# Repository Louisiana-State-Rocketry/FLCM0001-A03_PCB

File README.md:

# Eclipse_2_PCB
PCB Files for the Eclipse 2 Flight Computer.

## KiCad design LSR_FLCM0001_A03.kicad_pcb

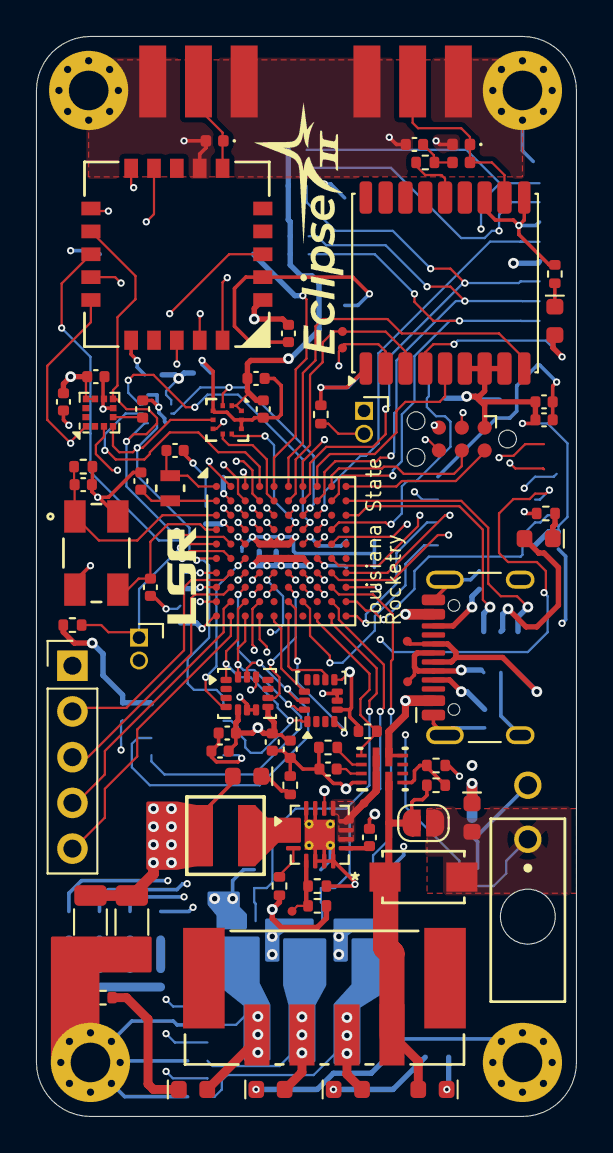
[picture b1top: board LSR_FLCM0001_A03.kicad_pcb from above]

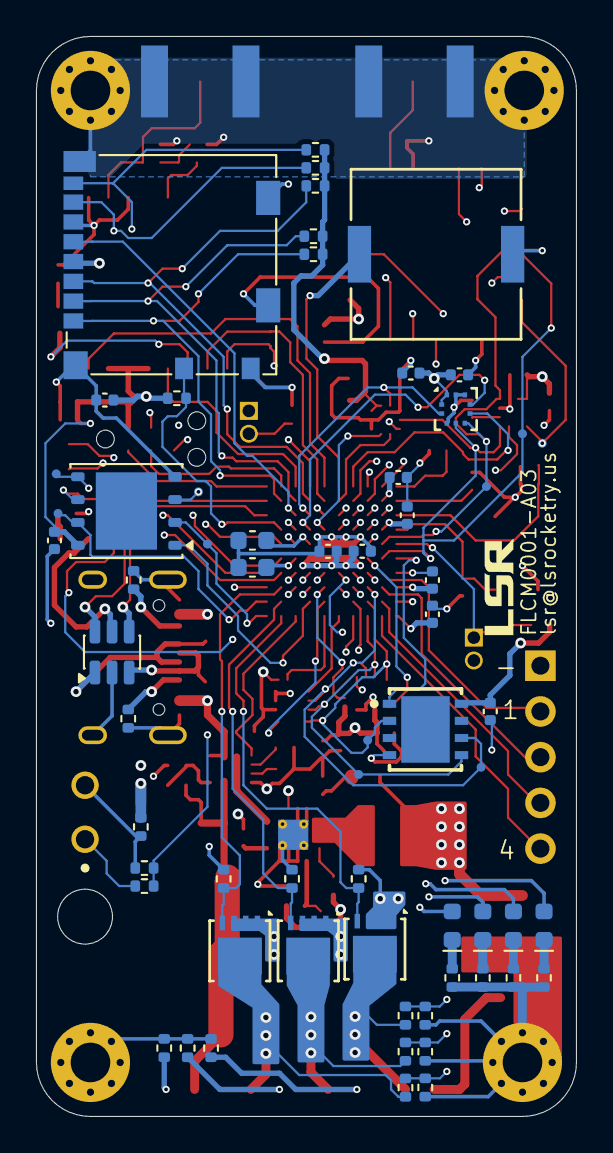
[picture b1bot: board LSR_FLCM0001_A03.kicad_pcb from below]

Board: 6 copper layers, 30.0 x 60.0 mm, 145 parts (63 on the bottom side), 111 nets.

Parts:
C1, C2: C_Small_US; C_0603_1608Metric
C3, C4, C5, C6, C7, C8, C9, C10, C11, C12, C13, C14, C15, C16, C17, C20, C21, C22, C23, C24, C25, C26, C27, C28, C29, C30, C31, C32, C34: C_Small_US; C_0402_1005Metric
C18, C19: C_Small_US; C_1206_3216Metric
C33: C_Small; C_0402_1005Metric
CR1: B340A-13-F; DIODE_SODB340_2P92X4P6_DIO
D1, D2, D5, D6, D9, D10, D11, D13: Yellow; LED_0603_1608Metric_Yellow
D3, D4, D7, D8: Red; LED_0603_1608Metric_Red
D12, D14: D_TVS_Small; D_0402_1005Metric
FB1: FerriteBead_Small; L_0402_1005Metric
H1, H2, H3, H4: MountingHole_2.2mm_M2_Pad_Via
IC1: FM25L04B-DG; SON95P400X450X80-9N-R270X370
J1: USB_C_Receptacle_USB2.0_16P; USB_C_Receptacle_HCTL_HC-TYPE-C-16P-01A
J2, J3: Conn_01x02_Pin; PinSocket_1x02_P1.27mm_Vertical
J4: Conn_ARM_SWD_TagConnect_TC2030-NL; Tag-Connect_TC2030-IDC-NL_2x03_P1.27mm_Vertical
J5: Micro_SD_Card_Det2; microSD_HC_Molex_104031-0811
J6: 2125280200; CONN_2125280000_02_MOL
J7: 1771114; CONN_1814728
J8: Conn_01x05_Pin; PinHeader_1x05_P2.54mm_Vertical
J9, J10: SMA_Edge; SMA_Edge_8mm
JP1: SolderJumper-2_P1.3mm_Open_RoundedPad1.0x1.5mm
L1: 2.2uH; IND_COILCRAFT_XAL4020
LS1: CPT-9019A-SMT-TR; CPT-9019A_CUD
Q1, Q2, Q3: AON7296; DFN3X3A_8L_EPA1_P_AOS
R1, R2, R3, R4, R5, R6, R7, R8, R9, R10, R11, R12, R13, R14, R15, R16, R17, R18, R19, R20, R21, R22, R23, R24, R25, R26, R27, R28, R29, R30, R31, R32, R33, R34, R35, R36, R37, R38, R39, R40, R41, R42: R_Small_US; R_0402_1005Metric
TP1, TP2, TP3, TP4, TP5, TP6, TP7, TP8, TP9, TP10, TP11, TP12, TP13, TP14, TP15, TP16, TP17, TP18: TestPoint; TestPoint-0.5mm
U1: USBLC6-2SC6; SOT-23-6
U2: STM32H742VGH6; TFBGA-100_8x8mm_Layout10x10_P0.8mm
U3: W25Q128JVP; WSON-8-1EP_6x5mm_P1.27mm_EP3.4x4.3mm
U4: TPS62130A; VQFN-16-1EP_3x3mm_P0.5mm_EP1.68x1.68mm_ThermalVias
U5: TPS2121RUXR; RUX0012A
U6: LSM6DSM; LGA-14_3x2.5mm_P0.5mm_LayoutBorder3x4y
U7: LSM6DS320; LGA-14_3x2.5mm_P0.5mm_LayoutBorder3x4y
U8: LIS2MDL; LGA-12_2x2mm_P0.5mm
U9, U10: BMP390; 10LGA_2X2X0p75_BOS
U11: MAX-M10S; ublox_MAX
U12: E22-900MM22S; E22-900MM22S_BYT
XTAL1: 9HT11-32.768KDZB-T; XTAL_68KDZB-T_TXC
Y1: ABM3B-24.000MHZ; CRYSTAL_ABM3B_ABR

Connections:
+3V3: C3.1, C4.1, C5.1, C6.1, C7.1, C8.1, C13.1, C14.1, C15.1, C18.1, C19.1, C20.1, C21.1, C22.1, C23.1, C24.1, C26.1, C27.1, C28.1, C29.1, C30.1, C31.1, C32.1, C34.1, D7.2 (A), IC1.8 (VDD), J3.1, J4.1 (VCC), J5.4 (VDD), L1.2, R3.2, R12.1, R13.1, R14.1, R15.1, R16.1, R17.2, R22.2, R24.2, R28.2, TP18.1 (1_1), U2.B2 (VBAT), U2.D2 (VDD), U2.F4 (VDDLDO), U2.F5 (VDD), U2.F6 (VDD33_USB), U2.F7 (PDR_ON), U2.H1 (VDDA), U2.K1 (VDD), U3.8 (VCC), U4.14 (VOS), U6.5 (VDDIO), U6.8 (VDD), U7.5 (VDDIO), U7.8 (VDD), U8.9 (Vdd), U8.10 (Vdd_IO), U9.1 (VDDIO), U9.10 (VDD), U10.1 (VDDIO), U10.10 (VDD), U11.6 (V_BCKP), U11.7 (VCC_IO), U11.8 (VCC), U12.1 (VCC)
/ADC1_INP4: R36.2, R37.2, U2.G4 (ADC1_INP4)
/ADC1_INP8: R32.2, R33.2, U2.H4 (ADC1_INP8)
/ADC1_INP9: R34.2, R35.2, U2.J4 (ADC1_INP9)
/BMP_{1}.INT: U2.D6 (PD7), U10.7 (INT)
/BMP_{2}.INT: U2.D7 (PD4), U9.7 (INT)
/Connectors/CC1: J1.A5 (CC1), R2.2
/Connectors/CC2: J1.B5 (CC2), R1.2
/Connectors/D+: J1.A6 (D+), J1.B6 (D+), TP3.1 (1_1), U1.1 (I/O1)
/Connectors/D-: J1.A7 (D-), J1.B7 (D-), TP2.1 (1_1), U1.3 (I/O2)
/EBYTE.BUSY: U2.B4 (PB8), U12.11 (BUSY)
/EBYTE.CS: U2.A2 (PC13), U12.14 (NSS)
/EBYTE.DIO1: U2.C5 (PB5), U12.20 (DIO1)
/EBYTE.DIO2: U2.B3 (PE3), U12.19 (DIO2)
/EBYTE.DIO3: U2.C3 (PE4), U12.18 (DIO3)
/EBYTE.NRST: U2.D3 (PE5), U12.3 (NRST)
/EBYTE.RXEN: U2.C4 (PE1), U12.10 (RXEN)
/EBYTE.TXEN: U2.D4 (PE0), U12.9 (TXEN)
/GPS.EXTINT: U2.A8 (PA15), U11.5 (EXTINT)
/GPS.~RESET: U2.A6 (PB4), U11.9 (~RESET)
/LIS2MDL.CS: U2.G3 (PA4), U8.3 (~CS)
/LSM6DSM.CS: U2.K5 (PE9), U6.12 (CS)
/LSM6DSM.INT1: U2.J6 (PE12), U6.4 (INT1)
/LSM6DSM.INT2: U2.K6 (PE13), U6.9 (INT2)
/LSM6DSV320XTR.CS: U2.G6 (PE10), U7.12 (CS)
/LSM6DSV320XTR.INT1: U2.F3 (PC3_C), U7.4 (INT1)
/LSM6DSV320XTR.INT2: U2.H6 (PE11), U7.9 (INT2)
/MCU/ADC_BATT: R5.1, R6.2, U2.K4 (ADC1_INP5)
/MCU/BATT_LED: D1.1 (K), R8.2
/MCU/BOOT0: J3.2, R4.2, U2.D5 (BOOT0)
/MCU/Buzzer_PWM: LS1.1, U2.A5 (TIM4_CH2)
/MCU/NRST: J2.1, J4.3 (~RESET), R3.1, U2.E1 (NRST)
/MCU/PD14: D1.2 (A), U2.H8 (PD14)
/MCU/PD15: D2.2 (A), U2.G8 (PD15)
/MCU/PE14: D3.2 (A), U2.G7 (PE14)
/MCU/PE15: D4.2 (A), U2.H7 (PE15)
/MCU/Power_LED_3V3: D3.1 (K), R10.2
/MCU/Power_LED_VIN: D4.1 (K), R11.2
/MCU/RCC_OSC32_IN: C11.1, U2.A1 (RCC_OSC32_IN), XTAL1.1
/MCU/RCC_OSC32_OUT: C12.1, U2.B1 (RCC_OSC32_OUT), XTAL1.2
/MCU/RCC_OSC_IN: C9.1, R7.2, U2.C1 (RCC_OSC_IN), Y1.1
/MCU/RCC_OSC_OUT: C10.1, U2.D1 (RCC_OSC_OUT), Y1.3
/MCU/SWCLK: J4.4 (SWCLK), U2.A9 (DEBUG_JTCK-SWCLK)
/MCU/SWDIO: J4.2 (SWDIO), U2.A10 (DEBUG_JTMS-SWDIO)
/MCU/SWO: J4.6 (SWO), U2.A7 (DEBUG_JTDO-SWO)
/MCU/USB_LED: D2.1 (K), R9.2
/MCU/VCAP1: C1.1, U2.E7 (VCAP)
/MCU/VCAP2: C2.1, U2.F8 (VCAP)
/Power/BATT_LED: D5.1 (K), R20.2
/Power/CP2: R18.1, R19.2, U5.3 (CP2)
/Power/FB: R24.1, R25.2, TP16.1 (1_1), U4.5 (FB)
/Power/ILM: R26.2, U5.10 (ILM)
/Power/PG: R22.1, U4.4 (PG)
/Power/Power_LED_3V3: D7.1 (K), R23.2
/Power/Power_LED_VIN: D8.1 (K), R27.2
/Power/SS: C17.1, U5.11 (SS)
/Power/SS/TR: C16.1, U4.9 (SS/TR)
/Power/TPS2121.SW: L1.1, U4.1 (SW), U4.2 (SW), U4.3 (SW)
/Power/USB_LED: D6.1 (K), R21.2
/Pyro/Pyro_{1}_Charge: D11.2 (A), J7.1, Q3.5, Q3.6, Q3.7, Q3.8, Q3.9, R36.1
/Pyro/Pyro_{1}_LED: D11.1 (K), R40.2
/Pyro/Pyro_{2}_Charge: D9.2 (A), J7.2, Q1.5, Q1.6, Q1.7, Q1.8, Q1.9, R32.1
/Pyro/Pyro_{2}_LED: D9.1 (K), R38.2
/Pyro/Pyro_{3}_Charge: D10.2 (A), J7.3, Q2.5, Q2.6, Q2.7, Q2.8, Q2.9, R34.1
/Pyro/Pyro_{3}_LED: D10.1 (K), R39.2
/Pyro_{1}_Gate: Q3.4, R31.1, U2.K9 (PD8)
/Pyro_{2}_Gate: Q1.4, R30.1, U2.J9 (PD9)
/Pyro_{3}_Gate: Q2.4, R29.1, U2.H9 (PD10)
/QUADSPI_BK1_IO0: TP7.1 (1_1), U2.G9 (QUADSPI_BK1_IO0), U3.5 (DI/IO_{0})
/QUADSPI_BK1_IO1: TP8.1 (1_1), U2.K10 (QUADSPI_BK1_IO1), U3.2 (DO/IO_{1})
/QUADSPI_BK1_IO2: TP4.1 (1_1), U2.A3 (QUADSPI_BK1_IO2), U3.3 (~WP/IO_{2})
/QUADSPI_BK1_IO3: TP9.1 (1_1), U2.J10 (QUADSPI_BK1_IO3), U3.7 (~HOLD/~RESET/IO_{3})
/QUADSPI_BK1_NCS: U2.J7 (QUADSPI_BK1_NCS), U3.1 (~CS)
/QUADSPI_CLK: U2.G5 (QUADSPI_CLK), U3.6 (CLK)
/SDMMC1_CK: J5.5 (CLK), U2.C8 (SDMMC1_CK)
/SDMMC1_CMD: J5.3 (CMD), R14.2, U2.B7 (SDMMC1_CMD)
/SDMMC1_D0: J5.7 (DAT0), R13.2, U2.F9 (SDMMC1_D0)
/SDMMC1_D1: J5.8 (DAT1), R12.2, U2.E9 (SDMMC1_D1)
/SDMMC1_D2: J5.1 (DAT2), R16.2, U2.B9 (SDMMC1_D2)
/SDMMC1_D3: J5.2 (DAT3/CD), R15.2, U2.B8 (SDMMC1_D3)
/SD_DET: J5.9 (DET_B), R17.1, U2.D9 (PA8)
/SPI1_MISO: IC1.2 (SO), TP11.1 (1_1), U2.J3 (SPI1_MISO), U6.1 (SDO/SA0), U7.1 (SDO/SA0)
/SPI1_MOSI: IC1.5 (SI), TP12.1 (1_1), U2.K3 (SPI1_MOSI), U6.14 (SDA), U7.14 (SDA)
/SPI1_SCK: IC1.6 (SCK), TP10.1 (1_1), U2.H3 (SPI1_SCK), U6.13 (SCL), U7.13 (SCL)
/SPI2_MISO: TP14.1 (1_1), U2.E2 (SPI2_MISO), U8.7 (DRDY), U9.5 (SDO), U10.5 (SDO), U12.12 (MISO)
/SPI2_MOSI: TP15.1 (1_1), U2.F2 (SPI2_MOSI), U8.4 (SDA/SDI/SDO), U9.4 (SDI), U10.4 (SDI), U12.13 (MOSI)
/SPI2_SCK: TP13.1 (1_1), U2.C7 (SPI2_SCK), U8.1 (SCL/SPC), U9.2 (SCK), U10.2 (SCK), U12.15 (SCK)
/ST: R28.1, U2.K8 (PB12), U5.9 (ST)
/Sensors/Magnetometer/C1: C25.1, U8.5 (C1)
/Sensors/RF/EBYTE.ANT: D12.1 (A1), J9.1 (In), U12.6 (ANT)
/Sensors/RF/GPS.RF_{Filter}: C33.1, FB1.2, R42.2
/Sensors/RF/GPS.TIMEPULSE: D13.2 (A), U11.4 (TIMEPULSE)
/Sensors/RF/RF_IN: D14.1 (A1), FB1.1, J10.1 (In), U11.11 (RF_IN)
/Sensors/RF/Timepulse_LED: D13.1 (K), R41.2
/Sensors/RF/VCC_RF: R42.1, U11.14 (VCC_RF)
/TIM2_CH1: J8.2, U2.G2 (TIM2_CH1)
/TIM2_CH2: J8.3, U2.H2 (TIM2_CH2)
/TIM2_CH3: J8.4, U2.J2 (TIM2_CH3)
/TIM2_CH4: J8.5, U2.K2 (TIM2_CH4)
/USART2_RX: TP6.1 (1_1), U2.C6 (USART2_RX), U11.2 (TXD)
/USART2_TX: TP5.1 (1_1), U2.B6 (USART2_TX), U11.3 (RXD)
/USB_OTG_FS_DM: U1.4 (I/O2), U2.C10 (USB_OTG_FS_DM)
/USB_OTG_FS_DP: U1.6 (I/O1), U2.B10 (USB_OTG_FS_DP)
/~BMP_{1.CS}: U2.B5 (PB6), U10.6 (CSB)
/~BMP_{2.CS}: U2.A4 (PB9), U9.6 (CSB)
/~FRAM.CS: IC1.1 (~CS), U2.F1 (PC0)
GND: C1.2, C2.2, C3.2, C4.2, C5.2, C6.2, C7.2, C8.2, C9.2, C10.2, C11.2, C12.2, C13.2, C14.2, C15.2, C16.2, C17.2, C18.2, C19.2, C20.2, C21.2, C22.2, C23.2, C24.2, C25.2, C26.2, C27.2, C28.2, C29.2, C30.2, C31.2, C32.2, C33.2, C34.2, D12.2 (A2), D14.2 (A2), H1.1, H2.1, H3.1, H4.1, IC1.4 (VSS), J1.A1 (GND), J1.A12 (GND), J1.B1 (GND), J1.B12 (GND), J1.SH (SHIELD), J2.2, J4.5 (GND), J5.6 (VSS), J5.10 (DET_A), J5.SH (SHIELD), J6.2, J8.1, J9.2 (Ext), J10.2 (Ext), LS1.2, Q1.1, Q1.2, Q1.3, Q2.1, Q2.2, Q2.3, Q3.1, Q3.2, Q3.3, R1.1, R2.1, R4.1, R6.1, R7.1, R8.1, R9.1, R10.1, R11.1, R19.1, R20.1, R21.1, R23.1, R25.1, R26.1, R27.1, R29.2, R30.2, R31.2, R33.1, R35.1, R37.1, R38.1, R39.1, R40.1, R41.1, U1.2 (GND), U2.C2 (VSS), U2.E4 (VSS), U2.E5 (VSS), U2.E6 (VSS), U2.G1 (VSSA), U2.J1 (VSS), U3.4 (GND), U4.6 (GND), U4.7 (FSW), U4.8 (DEF), U4.15 (GND), U4.16 (GND), U4.17 (GND), U5.12 (GND), U6.6 (GND), U6.7 (GND), U7.6 (GND), U7.7 (GND), U8.6 (GND), U8.8 (GND), U9.3 (VSS), U9.8 (VSS), U9.9 (VSS), U10.3 (VSS), U10.8 (VSS), U10.9 (VSS), U11.1 (GND), U11.10 (GND), U11.12 (GND), U12.2 (GND), U12.7 (GND), U12.16 (GND), Y1.2, Y1.4
VBATT: CR1.2, D5.2 (A), J6.1, JP1.1 (A), R5.2
VIN: CR1.1, D8.2 (A), J7.4, JP1.2 (B), R18.2, U5.2 (IN2)
VSW: TP17.1 (1_1), U4.10 (VIN), U4.11 (VIN), U4.12 (VIN), U4.13 (EN), U5.1 (OUT), U5.8 (OUT)
VUSB: D6.2 (A), J1.A4 (VBUS), J1.A9 (VBUS), J1.B4 (VBUS), J1.B9 (VBUS), TP1.1 (1_1), U1.5 (VBUS), U5.6 (PR1), U5.7 (IN1)
